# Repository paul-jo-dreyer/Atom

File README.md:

# The Atom Project Overview

Atom is a micro modular robot designed as a test platform for studying swarm robotics, including multi-agent planning, control, and coordination. Up to 10 Atom robots can be in play at a given time, acting independently, or collaboratively. Paired with an **overwatch** application, state update information is streamed to each of the robots in a group broadcast, enabling rapid, low cost localization of each bot within the environment. 

## Communications

Each Atom is connected to a local Wifi network. 

## Localization

Localization of the system is handled by an overwatch system, which identifies Apriltags attached to the compute-chunk of each robot, and to the base station.

# Case Studies

## 1v1 Soccer

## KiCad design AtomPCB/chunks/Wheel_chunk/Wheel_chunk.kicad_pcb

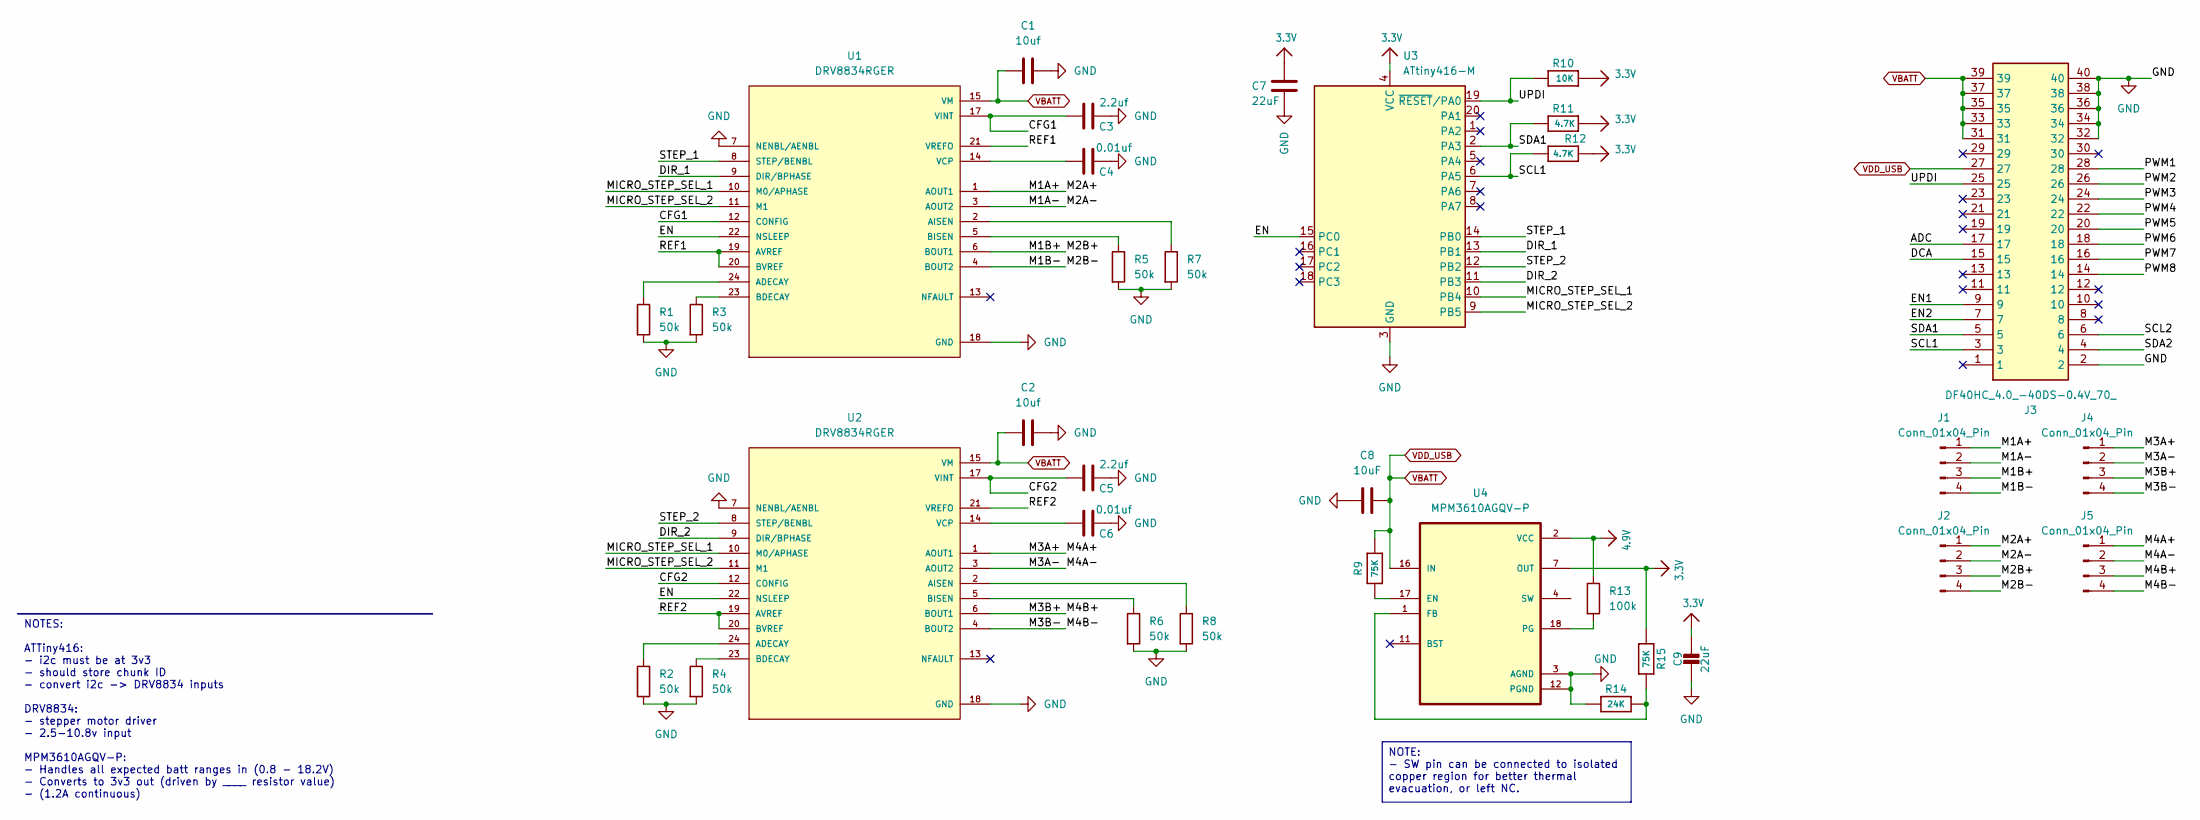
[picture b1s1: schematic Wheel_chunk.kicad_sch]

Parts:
C1, C2: 10uf; C_0805_2012Metric
C3, C5: 2.2uf; C_0805_2012Metric
C4, C6: 0.01uf; C_0805_2012Metric
C7, C9: 22uF; C_0805_2012Metric
C8: 10uF; C_0805_2012Metric
J1, J2, J4, J5: Conn_01x04_Pin; PAD_1x4_4.0x2.0
J3: DF40HC_4.0_-40DS-0.4V_70_; DF40HC4040DS04V70; Mouser Part Number 798-DF4HC4040DS04V70
R1, R2, R3, R4, R5, R6, R7, R8: 50k; R_0805_2012Metric
R9, R15: 75K; R_0805_2012Metric
R10: 10K; R_0805_2012Metric
R11, R12: 4.7K; R_0805_2012Metric
R13: 100k; R_0805_2012Metric
R14: 24K; R_0805_2012Metric
U1, U2: DRV8834RGER; DRIVER_DRV8834RGER; PARTREV D
U3: ATtiny416-M; VQFN-20-1EP_3x3mm_P0.4mm_EP1.7x1.7mm
U4: MPM3610AGQV-P; CONV_MPM3620AGQV-P; PARTREV 1.0

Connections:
3.3V: C7.2, C9.1, R10.2, R11.2, R12.2, R15.1, U3.4 (VCC), U4.7 (OUT), U4.8 (OUT), U4.9 (OUT), U4.20 (OUT)
4.9V: R13.1, U4.2 (VCC)
/ADC: J3.17
/CFG1: C3.1, U1.12 (CONFIG), U1.17 (VINT)
/CFG2: C5.1, U2.12 (CONFIG), U2.17 (VINT)
/DCA: J3.15
/DIR_1: U1.9 (DIR/BPHASE), U3.13 (PB1)
/DIR_2: U2.9 (DIR/BPHASE), U3.11 (PB3)
/EN: U1.22 (NSLEEP), U2.22 (NSLEEP), U3.15 (PC0)
/EN1: J3.9
/EN2: J3.7
/M1A+: J1.1, J2.1, U1.1 (AOUT1)
/M1A-: J1.2, J2.2, U1.3 (AOUT2)
/M1B+: J1.3, J2.3, U1.6 (BOUT1)
/M1B-: J1.4, J2.4, U1.4 (BOUT2)
/M3A+: J4.1, J5.1, U2.1 (AOUT1)
/M3A-: J4.2, J5.2, U2.3 (AOUT2)
/M3B+: J4.3, J5.3, U2.6 (BOUT1)
/M3B-: J4.4, J5.4, U2.4 (BOUT2)
/MICRO_STEP_SEL_1: U1.10 (M0/APHASE), U2.10 (M0/APHASE), U3.10 (PB4)
/MICRO_STEP_SEL_2: U1.11 (M1), U2.11 (M1), U3.9 (PB5)
/PWM1: J3.28
/PWM2: J3.26
/PWM3: J3.24
/PWM4: J3.22
/PWM5: J3.20
/PWM6: J3.18
/PWM7: J3.16
/PWM8: J3.14
/REF1: U1.19 (AVREF), U1.20 (BVREF), U1.21 (VREFO)
/REF2: U2.19 (AVREF), U2.20 (BVREF), U2.21 (VREFO)
/SCL1: J3.3, R12.1, U3.6 (PA5)
/SCL2: J3.6
/SDA1: J3.5, R11.1, U3.2 (PA3)
/SDA2: J3.4
/STEP_1: U1.8 (STEP/BENBL), U3.14 (PB0)
/STEP_2: U2.8 (STEP/BENBL), U3.12 (PB2)
/UPDI: J3.25, R10.1, U3.19 (~RESET/PA0)
GND: C1.2, C2.2, C3.2, C4.2, C5.2, C6.2, C7.1, C8.1, C9.2, J3.2, J3.32, J3.34, J3.36, J3.38, J3.40, R1.2, R2.2, R3.2, R4.2, R5.2, R6.2, R7.2, R8.2, R14.1, U1.7 (NENBL/AENBL), U1.18 (GND), U1.25 (GND), U1.25.1 (GND), U1.25.2 (GND), U1.25.3 (GND), U1.25.4 (GND), U1.25.5 (GND), U2.7 (NENBL/AENBL), U2.18 (GND), U2.25 (GND), U2.25.1 (GND), U2.25.2 (GND), U2.25.3 (GND), U2.25.4 (GND), U2.25.5 (GND), U3.3 (GND), U3.21 (GND), U4.3 (AGND), U4.12 (PGND), U4.13 (PGND), U4.14 (PGND)
unnamed: R1.1, U1.24 (ADECAY)
unnamed: R7.1, U1.2 (AISEN)
unnamed: R3.1, U1.23 (BDECAY)
unnamed: R5.1, U1.5 (BISEN)
unnamed: C4.1, U1.14 (VCP)
unnamed: R2.1, U2.24 (ADECAY)
unnamed: R8.1, U2.2 (AISEN)
unnamed: R4.1, U2.23 (BDECAY)
unnamed: R6.1, U2.5 (BISEN)
unnamed: C6.1, U2.14 (VCP)
unnamed: R9.2, U4.17 (EN)
unnamed: R14.2, R15.2, U4.1 (FB)
unnamed: R13.2, U4.18 (PG)
unnamed: U4.4 (SW), U4.5 (SW), U4.6 (SW), U4.19 (SW)
VBATT: C1.1, C2.1, C8.2, J3.27, J3.31, J3.33, J3.35, J3.37, J3.39, R9.1, U1.15 (VM), U1.16 (VM), U2.15 (VM), U2.16 (VM), U4.16 (IN)

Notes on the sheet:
NOTE: - SW pin can be connected to isolated copper region for better thermal evacuation, or left NC.
NOTES: ATTiny416: - i2c must be at 3v3 - should store chunk ID - convert i2c -> DRV8834 inputs DRV8834: - stepper motor driver - 2.5-10.8v input MPM3610AGQV-P: - Handles all expected batt ranges in (0.8 - 18.2V) - Converts to 3v3 out (driven by ____ resistor value) - (1.2A continuous)

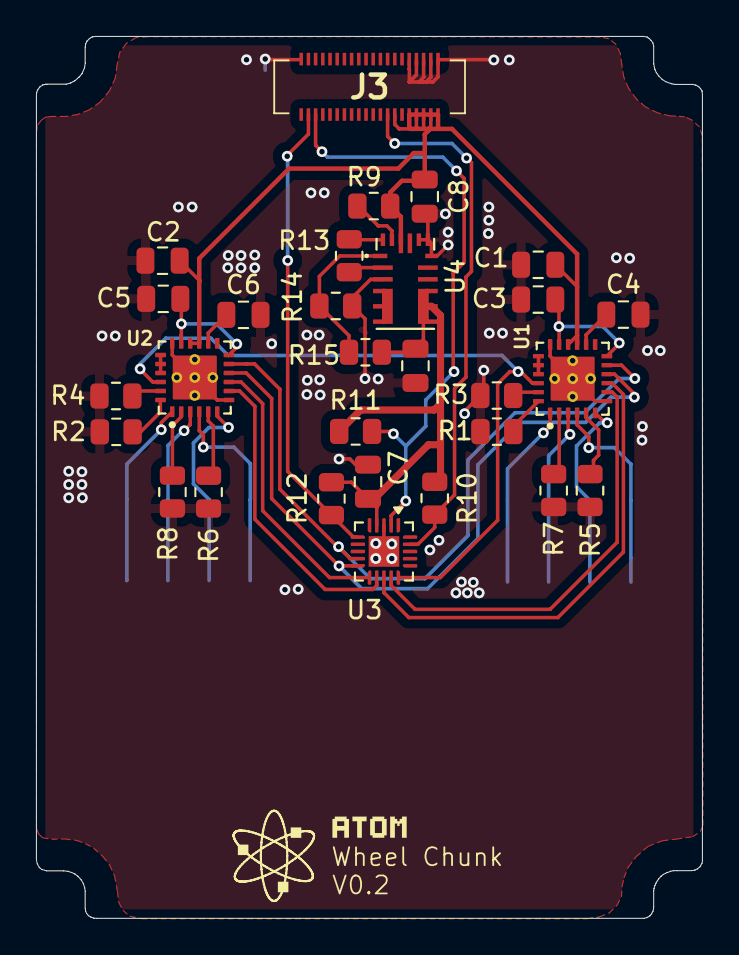
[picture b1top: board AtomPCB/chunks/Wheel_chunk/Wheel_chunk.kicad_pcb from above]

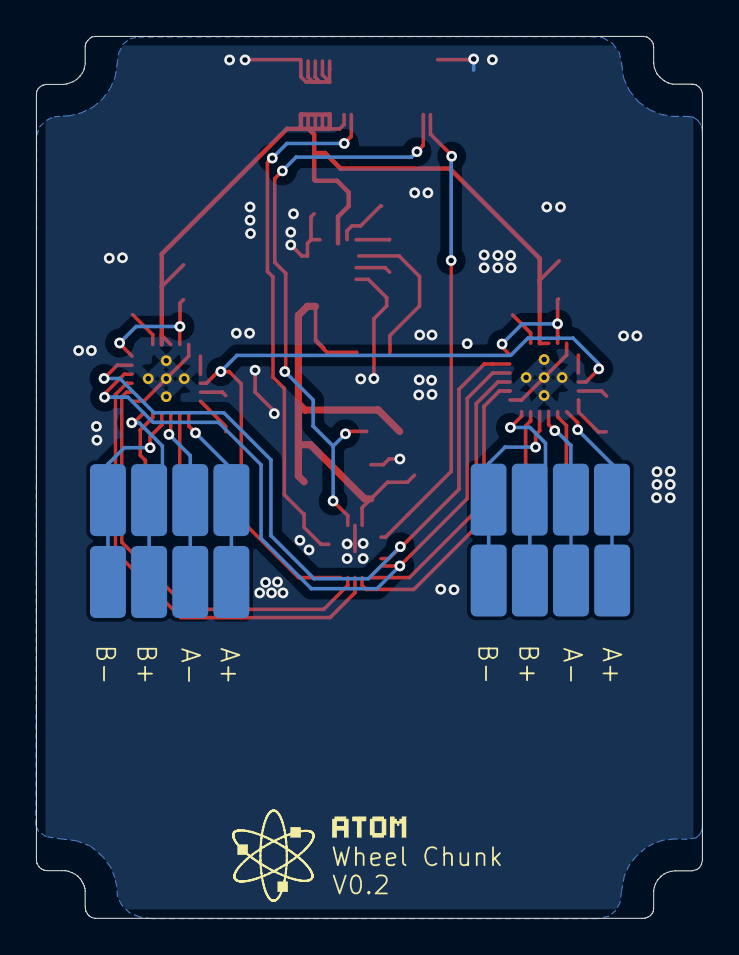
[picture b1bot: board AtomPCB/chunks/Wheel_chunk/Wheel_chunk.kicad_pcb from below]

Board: 2 copper layers, 37.0 x 49.0 mm, 33 parts (4 on the bottom side), 39 nets.

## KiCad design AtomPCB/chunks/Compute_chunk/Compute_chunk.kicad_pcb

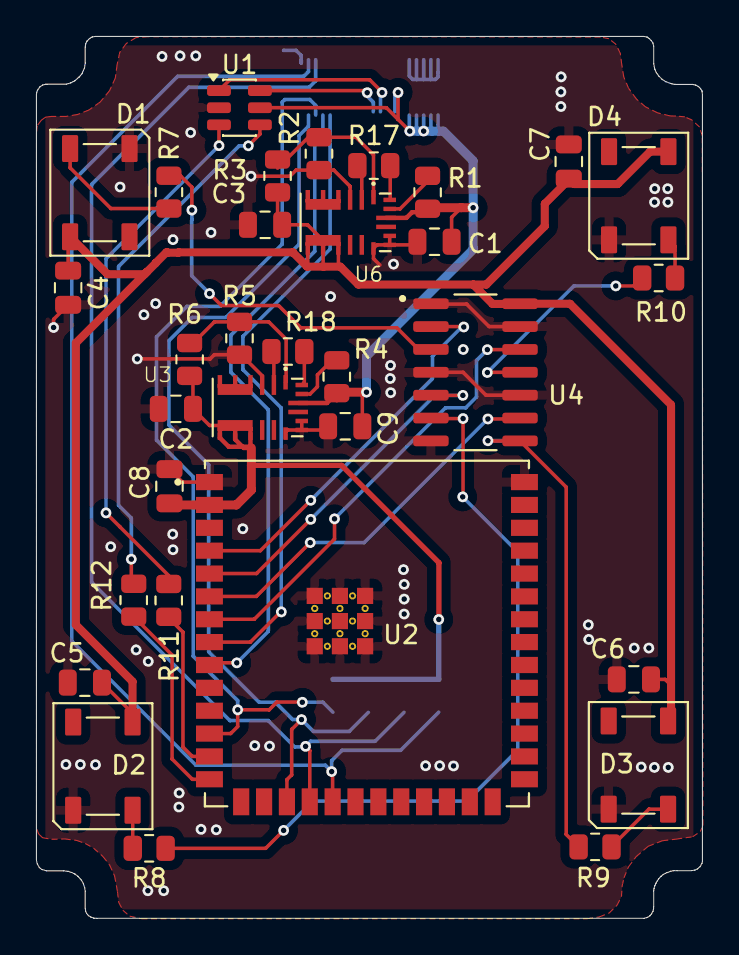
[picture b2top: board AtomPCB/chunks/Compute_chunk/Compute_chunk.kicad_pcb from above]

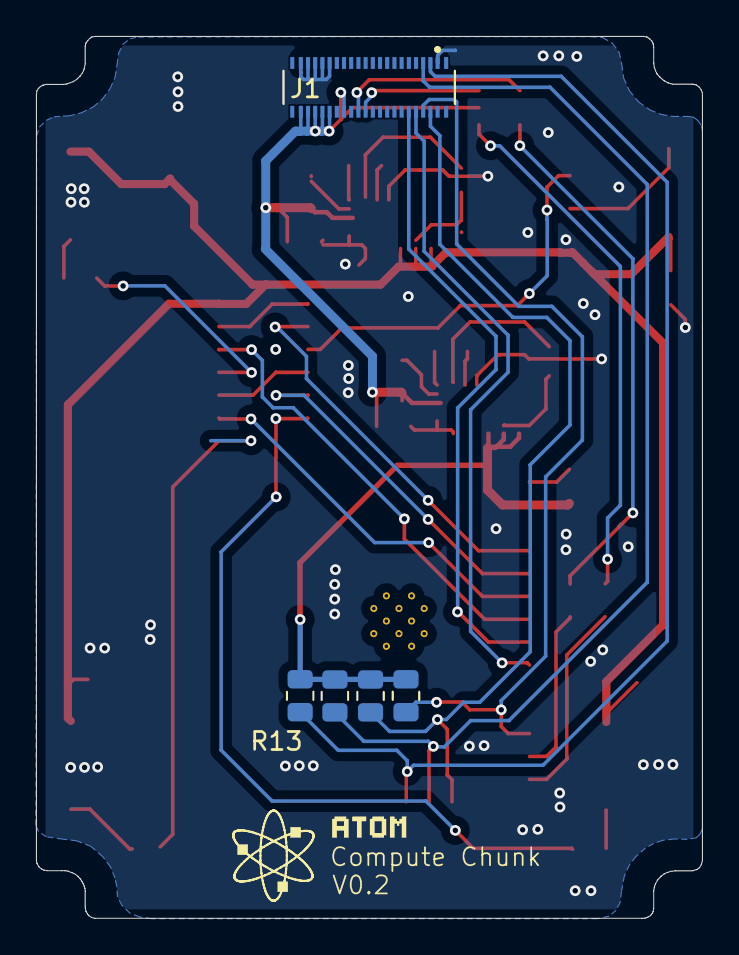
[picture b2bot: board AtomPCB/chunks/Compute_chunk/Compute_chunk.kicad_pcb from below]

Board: 2 copper layers, 37.0 x 49.0 mm, 37 parts (5 on the bottom side), 35 nets.

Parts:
C1, C9: 10uF; C_0805_2012Metric
C2, C3, C8: 22uF; C_0805_2012Metric
C4, C5, C6, C7: 0.1uF; C_0805_2012Metric
D1, D2, D3, D4: WS2812B; LED_WS2812B_PLCC4_5.0x5.0mm_P3.2mm
J1: DF40C-40DP-0.4V_51_; HRS_DF40C-40DP-0.4V_51_
R1, R4, R6: 75K; R_0805_2012Metric
R2: 19.1k; R_0805_2012Metric
R3, R17, R18: 100k; R_0805_2012Metric
R5: 24K; R_0805_2012Metric
R7, R8, R9, R10: 300; R_0805_2012Metric
R11, R12: 22; R_0805_2012Metric
R13, R14, R15, R16: 4.7K; R_0805_2012Metric
U1: USBLC6-2SC6; SOT-23-6
U2: ESP32-S3-WROOM-1U-N8R8; XCVR_ESP32-S3-WROOM-1U-N8R8
U3, U6: MPM3610AGQV-P; CONV_MPM3620AGQV-P
U4: SN74HCT125DR; SOIC127P600X175-14N

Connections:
3.3V: C2.1, C8.2, R6.1, R13.1, R14.2, R15.1, R16.1, U2.2 (3V3), U3.7 (OUT)
4.9V: R17.1, R18.1, U3.2 (VCC), U6.2 (VCC)
5.0V: C3.1, C4.2, C5.2, C6.2, C7.2, D1.1 (VDD), D2.1 (VDD), D3.1 (VDD), D4.1 (VDD), R3.1, U4.14 (VCC), U6.7 (OUT)
/DATA_D+: R12.2, U1.4 (I/O2)
/DATA_D-: R11.2, U1.3 (I/O2)
/EN1: J1.10, U2.8 (IO15)
/EN2: J1.8, U2.9 (IO16)
/LED1_CH: R7.1, U4.3 (1Y)
/LED1_CL: U2.4 (IO4), U4.2 (1A)
/LED2_CH: R8.1, U4.6 (2Y)
/LED2_CL: U2.5 (IO5), U4.5 (2A)
/LED3_CH: R9.1, U4.8 (3Y)
/LED3_CL: U2.6 (IO6), U4.9 (3A)
/LED4_CH: R10.1, U4.11 (4Y)
/LED4_CL: U2.7 (IO7), U4.12 (4A)
/SCL1: J1.4, R14.1, U2.17 (IO9)
/SCL2: J1.5, R15.2, U2.18 (IO10)
/SDA1: J1.6, R13.2, U2.12 (IO8)
/SDA2: J1.3, R16.2, U2.19 (IO11)
GND: C1.1, C2.2, C3.2, C4.1, C5.1, C6.1, C7.1, C8.1, C9.1, D1.3 (VSS), D2.3 (VSS), D3.3 (VSS), D4.3 (VSS), J1.1, J1.31, J1.33, J1.35, J1.37, J1.39, R2.1, R5.1, U1.2 (GND), U2.1 (GND), U2.40 (GND__1), U2.41_1 (GND__2), U2.41_2 (GND__3), U2.41_3 (GND__4), U2.41_4 (GND__5), U2.41_5 (GND__6), U2.41_6 (GND__7), U2.41_7 (GND__8), U2.41_8 (GND__9), U2.41_9 (GND__10), U3.3 (AGND), U3.12 (PGND), U3.13 (PGND), U3.14 (PGND), U4.1 (1~OE), U4.4 (2~OE), U4.7 (GND), U4.10 (3~OE), U4.13 (4~OE), U6.3 (AGND), U6.12 (PGND), U6.13 (PGND), U6.14 (PGND)
unnamed: D1.4 (DIN), R7.2
unnamed: D2.4 (DIN), R8.2
unnamed: D3.4 (DIN), R9.2
unnamed: D4.4 (DIN), R10.2
unnamed: J1.22, U1.6 (I/O1)
unnamed: J1.24, U1.1 (I/O1)
unnamed: R11.1, U2.13 (IO19)
unnamed: R12.1, U2.14 (IO20)
unnamed: R4.2, U3.17 (EN)
unnamed: R5.2, R6.2, U3.1 (FB)
unnamed: R18.2, U3.18 (PG)
unnamed: R1.2, U6.17 (EN)
unnamed: R2.2, R3.2, U6.1 (FB)
unnamed: R17.2, U6.18 (PG)
VBATT: C1.2, C9.2, J1.28, J1.32, J1.34, J1.36, J1.38, J1.40, R1.1, R4.1, U1.5 (VBUS), U3.16 (IN), U6.16 (IN)

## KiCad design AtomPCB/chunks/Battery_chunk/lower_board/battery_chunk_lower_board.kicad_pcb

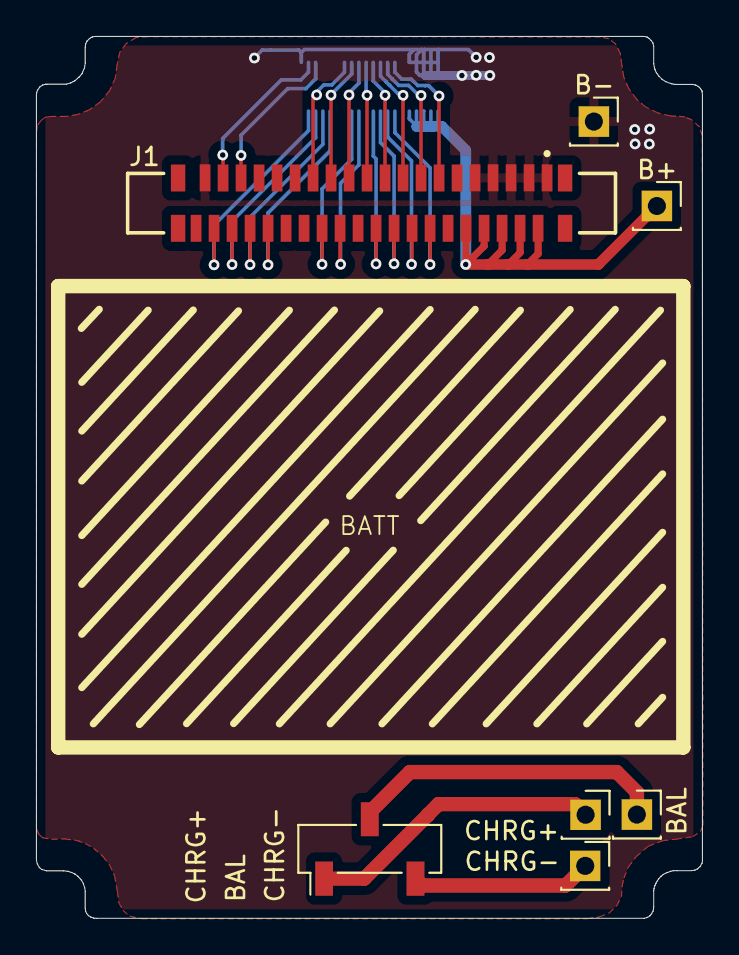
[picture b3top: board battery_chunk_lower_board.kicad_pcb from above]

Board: 2 copper layers, 37.0 x 49.0 mm, 8 parts (1 on the bottom side), 25 nets.

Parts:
B+: Conn_01x01_Pin; PinSocket_1x01_P2.54mm_Vertical
B-: Conn_01x01_Pin; PinSocket_1x01_P2.54mm_Vertical
BAL: Conn_01x01_Pin; PinSocket_1x01_P2.54mm_Vertical
CHRG+: Conn_01x01_Pin; PinSocket_1x01_P2.54mm_Vertical
CHRG-: Conn_01x01_Pin; PinSocket_1x01_P2.54mm_Vertical
J1: Conn_02x20_Odd_Even; GCT_FFC2A32-40-T
J7: DF40C-40DP-0.4V_51_; HRS_DF40C-40DP-0.4V_51_
J10: Conn_01x03_Pin; PinSocket_1x03_P2.54mm_Vertical_SMD_Pin1Left

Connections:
/Battery_chunk_lower/ADC: J1.24, J7.23
/Battery_chunk_lower/CHRG_+: CHRG+.1, J10.1
/Battery_chunk_lower/CHRG_-: CHRG-.1, J10.3
/Battery_chunk_lower/CHRG_BAL: BAL.1, J10.2
/Battery_chunk_lower/DATA_D+: J1.20, J7.19
/Battery_chunk_lower/DATA_D-: J1.18, J7.17
/Battery_chunk_lower/DCA: J1.26, J7.25
/Battery_chunk_lower/EN1: J1.32, J7.31
/Battery_chunk_lower/EN2: J1.34, J7.33
/Battery_chunk_lower/PWM1: J1.13, J7.14
/Battery_chunk_lower/PWM2: J1.15, J7.16
/Battery_chunk_lower/PWM3: J1.17, J7.18
/Battery_chunk_lower/PWM4: J1.19, J7.20
/Battery_chunk_lower/PWM5: J1.21, J7.22
/Battery_chunk_lower/PWM6: J1.23, J7.24
/Battery_chunk_lower/PWM7: J1.25, J7.26
/Battery_chunk_lower/PWM8: J1.27, J7.28
/Battery_chunk_lower/SCL1: J1.38, J7.37
/Battery_chunk_lower/SCL2: J1.35, J7.36
/Battery_chunk_lower/SDA1: J1.36, J7.35
/Battery_chunk_lower/SDA2: J1.37, J7.38
/Battery_chunk_lower/UDPI: J1.16, J7.15
GND: B-.1, J1.1, J1.3, J1.5, J1.7, J1.9, J1.39, J7.2, J7.4, J7.6, J7.8, J7.10, J7.40
VBATT: B+.1, J1.2, J1.4, J1.6, J1.8, J1.10, J7.1, J7.3, J7.5, J7.7, J7.9
VDD_USB: J1.14, J7.13

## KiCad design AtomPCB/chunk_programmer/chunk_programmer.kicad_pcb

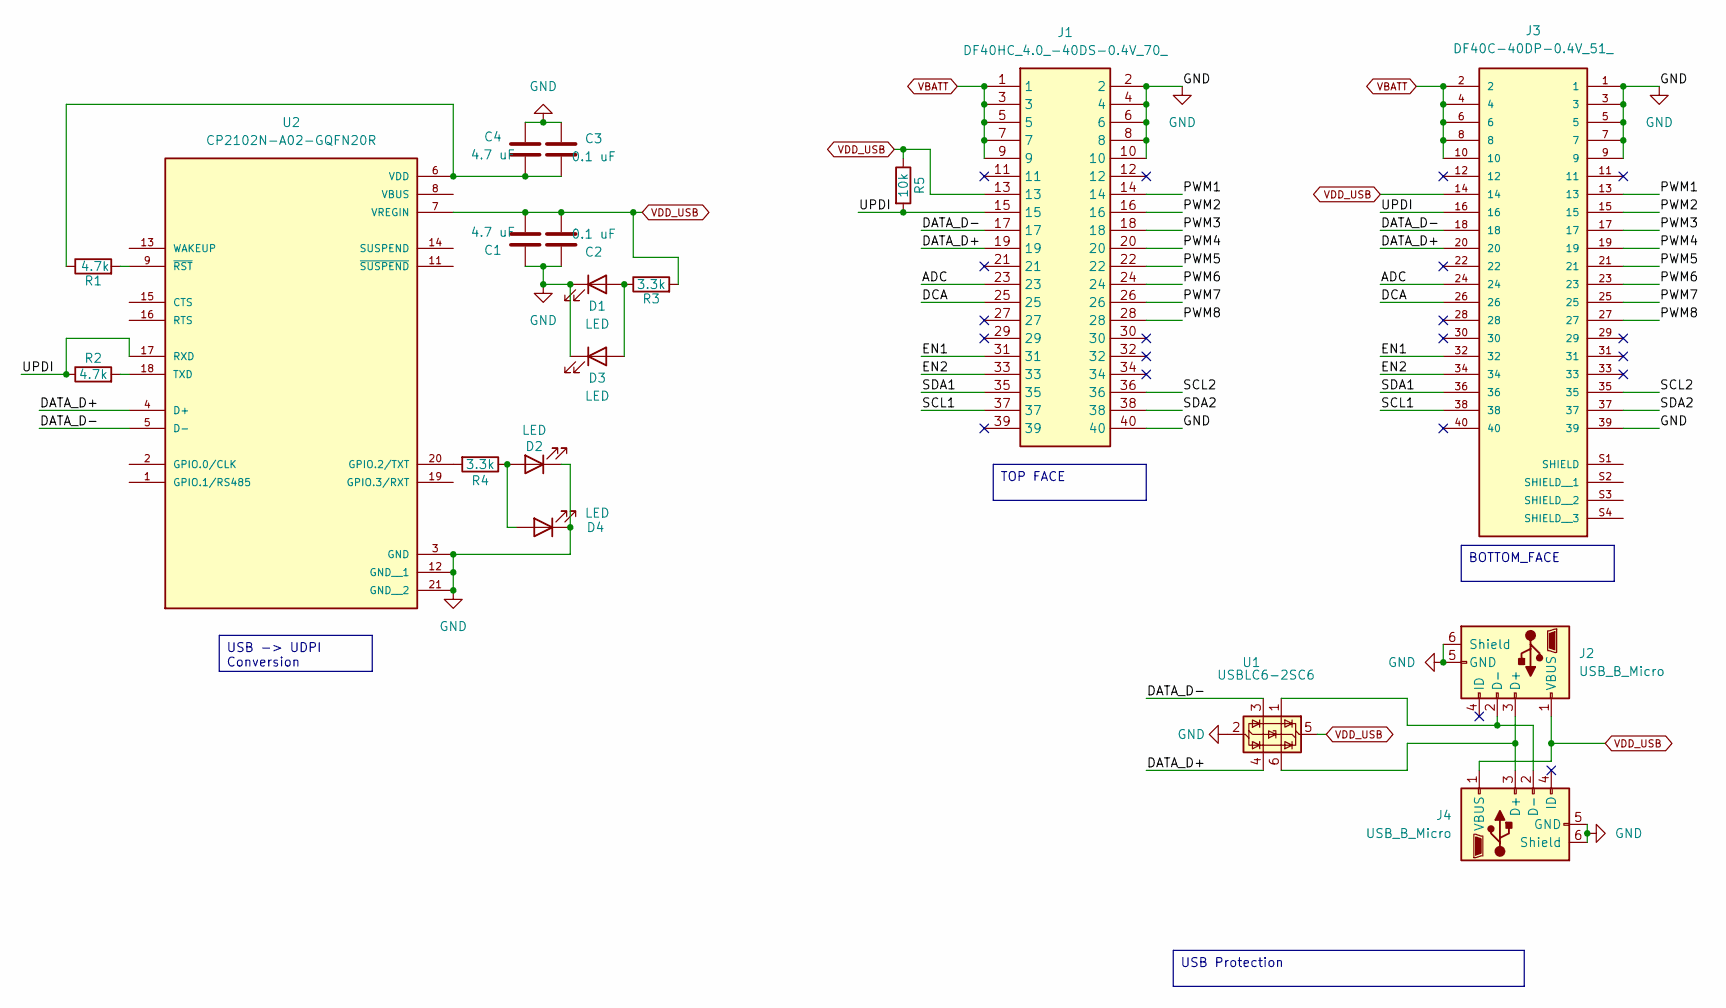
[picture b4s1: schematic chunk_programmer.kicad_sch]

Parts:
C1, C4: 4.7 uF; C_0805_2012Metric
C2, C3: 0.1 uF; C_0805_2012Metric
D1, D2, D3, D4: LED; LED_0603_1608Metric
J1: DF40HC_4.0_-40DS-0.4V_70_; DF40HC4040DS04V70; Mouser Part Number 798-DF4HC4040DS04V70
J2, J4: USB_B_Micro; USB_Micro-B_Amphenol_10118194_Horizontal
J3: DF40C-40DP-0.4V_51_; HRS_DF40C-40DP-0.4V_51_
R1, R2: 4.7k; R_0805_2012Metric
R3, R4: 3.3k; R_0805_2012Metric
R5: 10k; R_0805_2012Metric
U1: USBLC6-2SC6; SOT-23-6
U2: CP2102N-A02-GQFN20R; SILABS_CP2102N-A02-GQFN20R; PARTREV 1.3

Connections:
/ADC: J1.23, J3.24
/DATA_D+: J1.19, J3.20, U1.4 (I/O2), U2.4 (D+)
/DATA_D-: J1.17, J3.18, U1.3 (I/O2), U2.5 (D-)
/DCA: J1.25, J3.26
/EN1: J1.31, J3.32
/EN2: J1.33, J3.34
/PWM1: J1.14, J3.13
/PWM2: J1.16, J3.15
/PWM3: J1.18, J3.17
/PWM4: J1.20, J3.19
/PWM5: J1.22, J3.21
/PWM6: J1.24, J3.23
/PWM7: J1.26, J3.25
/PWM8: J1.28, J3.27
/SCL1: J1.37, J3.38
/SCL2: J1.36, J3.35
/SDA1: J1.35, J3.36
/SDA2: J1.38, J3.37
/UPDI: J1.15, J3.16, R2.1, R5.2, U2.17 (RXD)
GND: C1.1, C2.1, C3.1, C4.1, D1.1 (K), D2.1 (K), D3.1 (K), D4.1 (K), J1.2, J1.4, J1.6, J1.8, J1.10, J1.40, J2.5 (GND), J2.6 (Shield), J3.1, J3.3, J3.5, J3.7, J3.9, J3.39, J4.5 (GND), J4.6 (Shield), U1.2 (GND), U2.3 (GND), U2.12 (GND__1), U2.21 (GND__2)
unnamed: D1.2 (A), D3.2 (A), R3.1
unnamed: D2.2 (A), D4.2 (A), R4.1
unnamed: J2.3 (D+), J4.3 (D+), U1.6 (I/O1)
unnamed: J2.2 (D-), J4.2 (D-), U1.1 (I/O1)
unnamed: R4.2, U2.20 (GPIO.2/TXT)
unnamed: R2.2, U2.18 (TXD)
unnamed: C3.2, C4.2, R1.1, U2.6 (VDD)
unnamed: R1.2, U2.9 (~RST)
VBATT: J1.1, J1.3, J1.5, J1.7, J1.9, J3.2, J3.4, J3.6, J3.8, J3.10
VDD_USB: C1.2, C2.2, J1.13, J2.1 (VBUS), J3.14, J4.1 (VBUS), R3.2, R5.1, U1.5 (VBUS), U2.7 (VREGIN)

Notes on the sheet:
BOTTOM_FACE
USB Protection
USB -> UDPI Conversion
TOP FACE

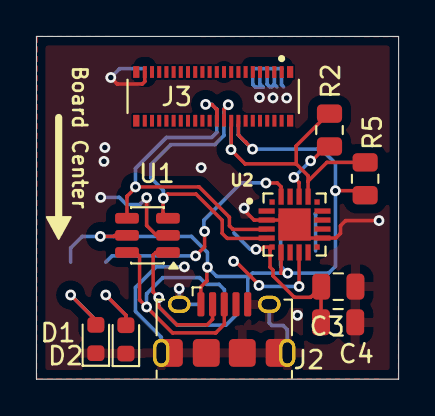
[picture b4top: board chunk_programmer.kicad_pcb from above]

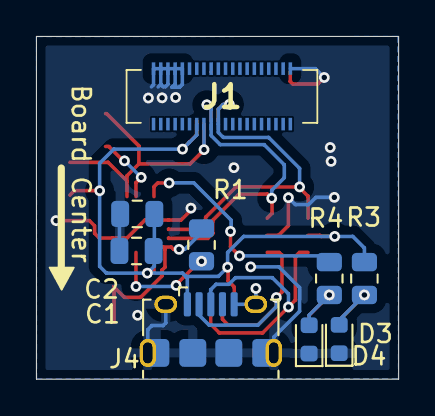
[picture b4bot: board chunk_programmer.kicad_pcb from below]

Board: 2 copper layers, 20.1 x 19.0 mm, 19 parts (9 on the bottom side), 30 nets.

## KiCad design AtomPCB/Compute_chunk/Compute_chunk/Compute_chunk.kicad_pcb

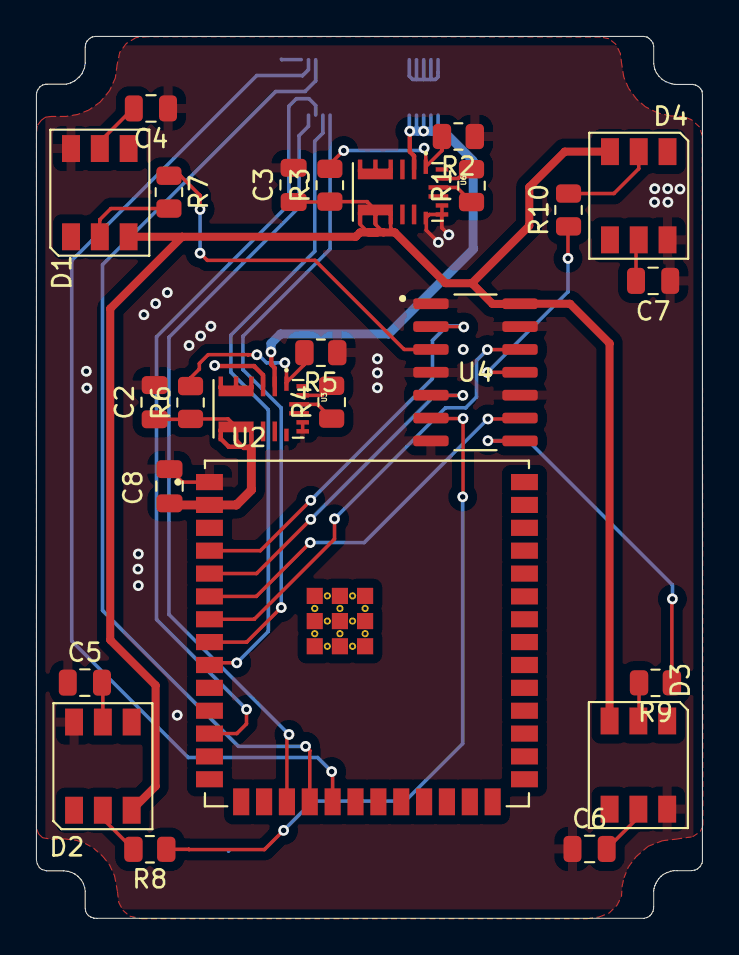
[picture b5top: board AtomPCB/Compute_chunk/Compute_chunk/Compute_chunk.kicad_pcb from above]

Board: 2 copper layers, 37.0 x 49.0 mm, 26 parts (1 on the bottom side), 33 nets.

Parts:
C2, C3: 22uF; C_0805_2012Metric
C4, C5, C6, C7: 0.1uF; C_0805_2012Metric
C8: 22uf; C_0805_2012Metric
D1, D2, D3, D4: WS2812; LED_WS2812_PLCC6_5.0x5.0mm_P1.6mm
J1: DF40HC_4.0_-40DS-0.4V_70_; DF40HC4040DS04V70
R1, R4, R6: 75K; R_0805_2012Metric
R2: 20K; R_0805_2012Metric
R3: 105K; R_0805_2012Metric
R5: 24K; R_0805_2012Metric
R7, R8, R9, R10: 300; R_0805_2012Metric
U2: ESP32-S3-WROOM-1U-N8R8; XCVR_ESP32-S3-WROOM-1U-N8R8
U3, U6: MPM3610AGQV-P; CONV_MPM3620AGQV-P
U4: SN74HCT125DR; SOIC127P600X175-14N

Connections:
3.3V: C2.1, C8.2, R6.1, U2.2 (3V3), U3.7 (OUT), U3.8 (OUT), U3.9 (OUT), U3.20 (OUT)
5.0V: C3.1, D1.3 (VCC), D2.3 (VCC), D3.3 (VCC), D4.3 (VCC), R3.1, U4.14 (VCC), U6.7 (OUT), U6.8 (OUT), U6.9 (OUT), U6.20 (OUT)
/EN1: J1.31, U2.8 (IO15)
/EN2: J1.33, U2.9 (IO16)
/LED1_CH: R7.1, U4.3 (1Y)
/LED1_CL: U2.4 (IO4), U4.2 (1A)
/LED2_CH: R8.1, U4.6 (2Y)
/LED2_CL: U2.5 (IO5), U4.5 (2A)
/LED3_CH: R9.1, U4.8 (3Y)
/LED3_CL: U2.6 (IO6), U4.9 (3A)
/LED4_CH: R10.1, U4.11 (4Y)
/LED4_CL: U2.7 (IO7), U4.12 (4A)
/SCL1: J1.37, U2.17 (IO9)
/SCL2: J1.36, U2.18 (IO10)
/SDA1: J1.35, U2.12 (IO8)
/SDA2: J1.38, U2.19 (IO11)
GND: C2.2, C3.2, C4.1, C5.1, C6.1, C7.1, C8.1, D1.6 (VSS), D2.6 (VSS), D3.6 (VSS), D4.6 (VSS), J1.2, J1.4, J1.6, J1.8, J1.10, J1.40, R2.1, R5.1, U2.1 (GND), U3.3 (AGND), U3.12 (PGND), U3.13 (PGND), U3.14 (PGND), U4.1 (1~OE), U4.4 (2~OE), U4.7 (GND), U4.10 (3~OE), U4.13 (4~OE), U6.3 (AGND), U6.12 (PGND), U6.13 (PGND), U6.14 (PGND)
unnamed: D1.2 (DIN), R7.2
unnamed: C4.2, D1.5 (VDD)
unnamed: D2.2 (DIN), R8.2
unnamed: C5.2, D2.5 (VDD)
unnamed: D3.2 (DIN), R9.2
unnamed: C6.2, D3.5 (VDD)
unnamed: D4.2 (DIN), R10.2
unnamed: C7.2, D4.5 (VDD)
unnamed: R4.2, U3.17 (EN)
unnamed: R5.2, R6.2, U3.1 (FB)
unnamed: U3.4 (SW), U3.5 (SW), U3.6 (SW), U3.19 (SW)
unnamed: R1.2, U6.17 (EN)
unnamed: R2.2, R3.2, U6.1 (FB)
unnamed: U6.4 (SW), U6.5 (SW), U6.6 (SW), U6.19 (SW)
VBATT: J1.1, J1.3, J1.5, J1.7, J1.9, U3.2 (VCC), U6.2 (VCC)
VIN: R1.1, R4.1, U3.16 (IN), U6.16 (IN)

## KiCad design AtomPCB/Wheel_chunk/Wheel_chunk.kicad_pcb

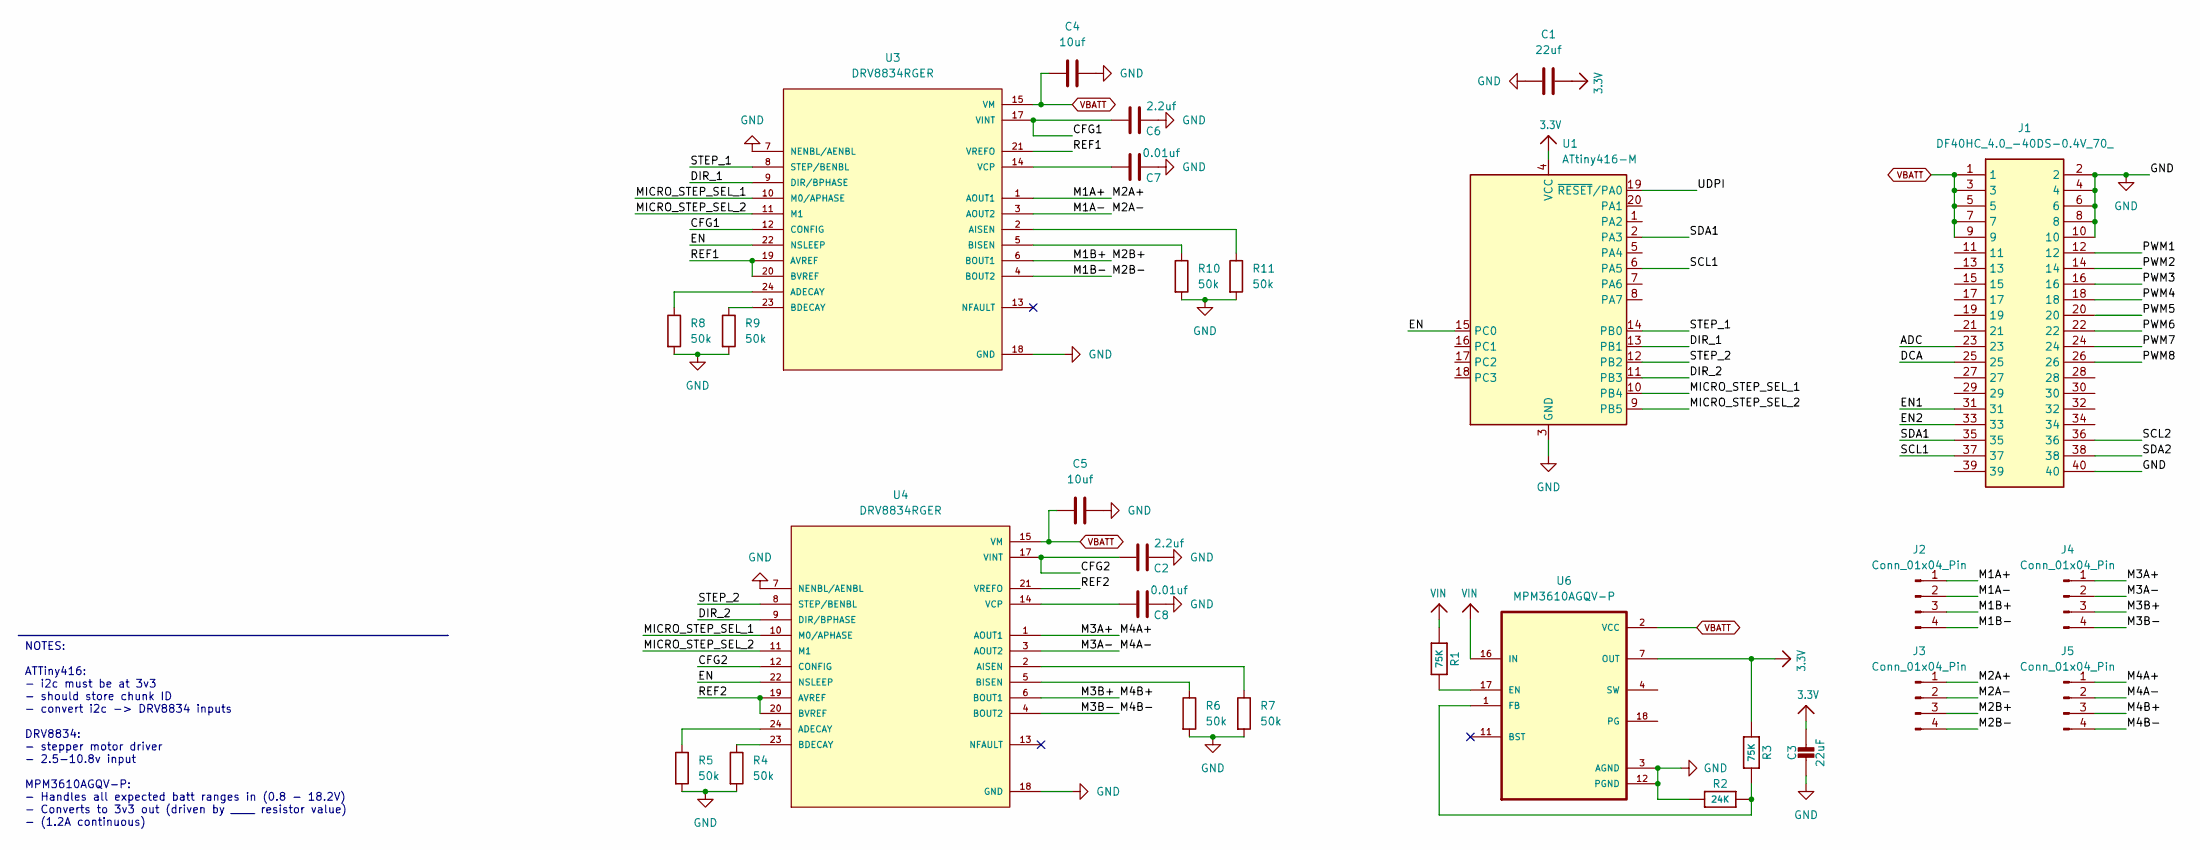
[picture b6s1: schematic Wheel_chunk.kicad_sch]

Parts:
C1: 22uf; C_0805_2012Metric
C2, C6: 2.2uf; C_0805_2012Metric
C3: 22uF; C_0805_2012Metric
C4, C5: 10uf; C_0805_2012Metric
C7, C8: 0.01uf; C_0805_2012Metric
J1: DF40HC_4.0_-40DS-0.4V_70_; DF40HC4040DS04V70; Mouser Part Number 798-DF4HC4040DS04V70
J2, J3, J4, J5: Conn_01x04_Pin; PAD_1x4_4.0x2.0
R1, R3: 75K; R_0805_2012Metric
R2: 24K; R_0805_2012Metric
R4, R5, R6, R7, R8, R9, R10, R11: 50k; R_0805_2012Metric
U1: ATtiny416-M; VQFN-20-1EP_3x3mm_P0.4mm_EP1.7x1.7mm
U3, U4: DRV8834RGER; DRIVER_DRV8834RGER; PARTREV D
U6: MPM3610AGQV-P; CONV_MPM3620AGQV-P; PARTREV 1.0

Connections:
3.3V: C1.2, C3.1, R3.1, U1.4 (VCC), U6.7 (OUT), U6.8 (OUT), U6.9 (OUT), U6.20 (OUT)
/ADC: J1.23
/CFG1: C6.1, U3.12 (CONFIG), U3.17 (VINT)
/CFG2: C2.1, U4.12 (CONFIG), U4.17 (VINT)
/DCA: J1.25
/DIR_1: U1.13 (PB1), U3.9 (DIR/BPHASE)
/DIR_2: U1.11 (PB3), U4.9 (DIR/BPHASE)
/EN: U1.15 (PC0), U3.22 (NSLEEP), U4.22 (NSLEEP)
/EN1: J1.31
/EN2: J1.33
/M1A+: J2.1, J3.1, U3.1 (AOUT1)
/M1A-: J2.2, J3.2, U3.3 (AOUT2)
/M1B+: J2.3, J3.3, U3.6 (BOUT1)
/M1B-: J2.4, J3.4, U3.4 (BOUT2)
/M3A+: J4.1, J5.1, U4.1 (AOUT1)
/M3A-: J4.2, J5.2, U4.3 (AOUT2)
/M3B+: J4.3, J5.3, U4.6 (BOUT1)
/M3B-: J4.4, J5.4, U4.4 (BOUT2)
/MICRO_STEP_SEL_1: U1.10 (PB4), U3.10 (M0/APHASE), U4.10 (M0/APHASE)
/MICRO_STEP_SEL_2: U1.9 (PB5), U3.11 (M1), U4.11 (M1)
/PWM1: J1.12
/PWM2: J1.14
/PWM3: J1.16
/PWM4: J1.18
/PWM5: J1.20
/PWM6: J1.22
/PWM7: J1.24
/PWM8: J1.26
/REF1: U3.19 (AVREF), U3.20 (BVREF), U3.21 (VREFO)
/REF2: U4.19 (AVREF), U4.20 (BVREF), U4.21 (VREFO)
/SCL1: J1.37, U1.6 (PA5)
/SCL2: J1.36
/SDA1: J1.35, U1.2 (PA3)
/SDA2: J1.38
/STEP_1: U1.14 (PB0), U3.8 (STEP/BENBL)
/STEP_2: U1.12 (PB2), U4.8 (STEP/BENBL)
/UDPI: U1.19 (~RESET/PA0)
GND: C1.1, C2.2, C3.2, C4.2, C5.2, C6.2, C7.2, C8.2, J1.2, J1.4, J1.6, J1.8, J1.10, J1.40, R2.1, R4.2, R5.2, R6.2, R7.2, R8.2, R9.2, R10.2, R11.2, U1.3 (GND), U1.21 (GND), U3.7 (NENBL/AENBL), U3.18 (GND), U3.25 (GND), U3.25.1 (GND), U3.25.2 (GND), U3.25.3 (GND), U3.25.4 (GND), U3.25.5 (GND), U4.7 (NENBL/AENBL), U4.18 (GND), U4.25 (GND), U4.25.1 (GND), U4.25.2 (GND), U4.25.3 (GND), U4.25.4 (GND), U4.25.5 (GND), U6.3 (AGND), U6.12 (PGND), U6.13 (PGND), U6.14 (PGND)
unnamed: R8.1, U3.24 (ADECAY)
unnamed: R11.1, U3.2 (AISEN)
unnamed: R9.1, U3.23 (BDECAY)
unnamed: R10.1, U3.5 (BISEN)
unnamed: C7.1, U3.14 (VCP)
unnamed: R5.1, U4.24 (ADECAY)
unnamed: R7.1, U4.2 (AISEN)
unnamed: R4.1, U4.23 (BDECAY)
unnamed: R6.1, U4.5 (BISEN)
unnamed: C8.1, U4.14 (VCP)
unnamed: R1.2, U6.17 (EN)
unnamed: R2.2, R3.2, U6.1 (FB)
unnamed: U6.4 (SW), U6.5 (SW), U6.6 (SW), U6.19 (SW)
VBATT: C4.1, C5.1, J1.1, J1.3, J1.5, J1.7, J1.9, U3.15 (VM), U3.16 (VM), U4.15 (VM), U4.16 (VM), U6.2 (VCC)
VIN: R1.1, U6.16 (IN)

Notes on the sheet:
NOTES: ATTiny416: - i2c must be at 3v3 - should store chunk ID - convert i2c -> DRV8834 inputs DRV8834: - stepper motor driver - 2.5-10.8v input MPM3610AGQV-P: - Handles all expected batt ranges in (0.8 - 18.2V) - Converts to 3v3 out (driven by ____ resistor value) - (1.2A continuous)

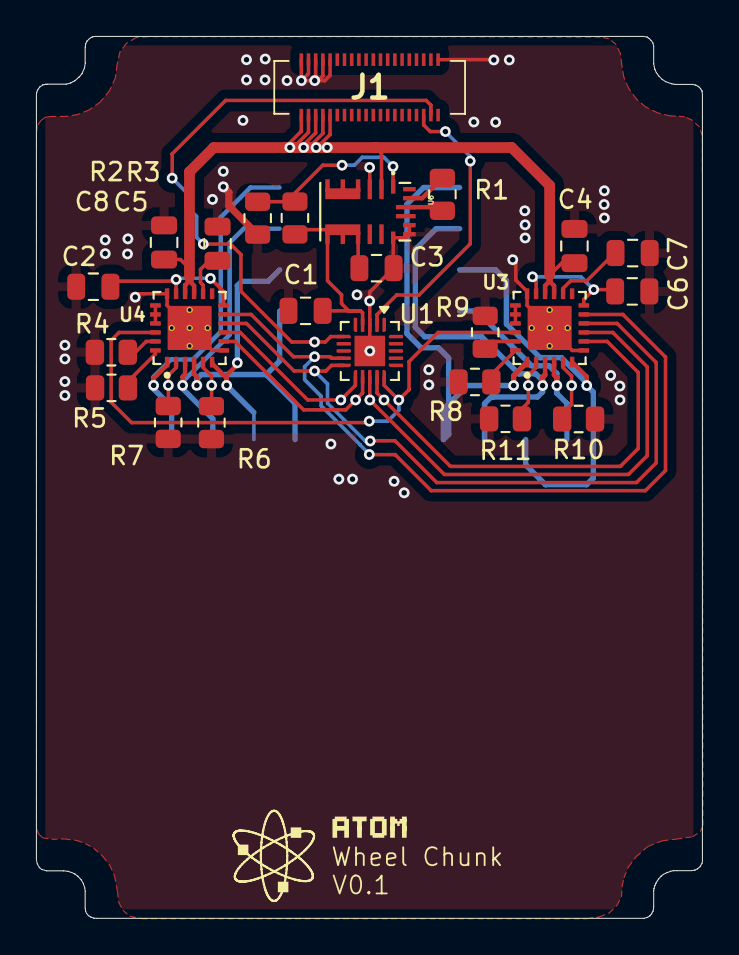
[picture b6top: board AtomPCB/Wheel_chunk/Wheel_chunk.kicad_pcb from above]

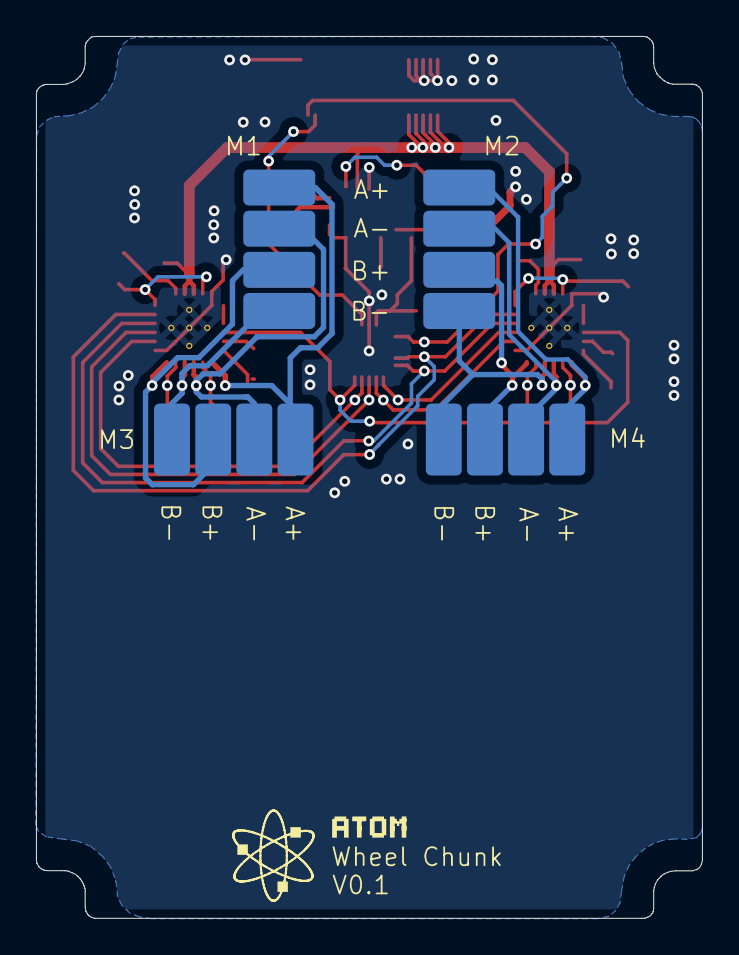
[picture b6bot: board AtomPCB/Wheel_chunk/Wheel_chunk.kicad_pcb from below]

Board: 2 copper layers, 37.0 x 49.0 mm, 28 parts (4 on the bottom side), 38 nets.

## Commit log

2026-04-11 intial commit - single april tag working with some minor bugs on android
2026-04-11 adding ignore
2026-04-11 adding index tag id printing to display. added april tag pdf. modified ignore to add gradle files
2026-04-11 added relative transforms to orgidin tag (id 0).
2026-04-13 adding logo
2026-04-15 First wheel chunk pcb commit! Basic component sleection + schematic. whooho!
2026-04-19 adding core pcb templates. Finished rev 0.1 of wheel chunk pcb
2026-04-19 deleting old templatees
2026-04-20 initial pass on compute chunk completed.
2026-04-27 first pcb panel order placed!
2026-04-27 adding claude readme for simulation / RL setup
2026-04-27 make and uv files
2026-04-27 updating ignore
2026-04-27 initial c bindings and build tests
2026-04-27 dynamics tex documentation set up
2026-04-27 adding manipulators and ball dynamics
2026-04-27 adding teleop py demo
2026-04-27 fixed bug with 'passthrough' manipulators
2026-04-28 enable multi robots in frame, add control input indicators to the header
2026-04-28 improving goal areas
2026-04-28 improve color profile
2026-04-28 adding gif generation test script
2026-04-28 add replay with scrub, update docs
2026-04-29 adding gym env, and action_observation. Using view cls instead of subclassing numpy this time
2026-04-29 adding basic reward terms
2026-04-29 first training run success!
2026-04-30 adding collisions to sim output. Adding sub proc sweeps to optimize through put
2026-04-30 adding orient towards ball reward.
2026-05-01 adding resume feature to argparse.
2026-05-01 adding net markings
2026-05-02 introduced team play. added sigmoid rolloff for boundary / goal box saftey distances.
2026-05-02 adding orientation biasing to ball_orientation reward.
2026-05-04 adding time-based goalie box rule to play + respective reward signal. extended obs dim by 1 to introduce time param per robot. Moved to yaml config instead of pure cli arg parse
2026-05-04 adding turf strips (aesthetic change only)
2026-05-04 updating buck converter footprint to proper pin definitions
2026-05-04 updated compute chunk schematic to introduce missing resistor and capacitor. Changed diff resistor values on 3v3 buck
2026-05-10 style updates + new icon
2026-05-10 improvments to device cards, + particle filter on feild frame estimation
2026-05-10 adding ball tracking + state broadcast
2026-05-10 deferred weights to yaml config file
2026-05-10 updating visualization of sim
2026-05-10 added scoreboard.
2026-05-16 comput chunk updates, fixing buck converter issues
2026-05-16 adding wheel chunk updates, fixing buck wiring issues
2026-05-16 Ui fixes
